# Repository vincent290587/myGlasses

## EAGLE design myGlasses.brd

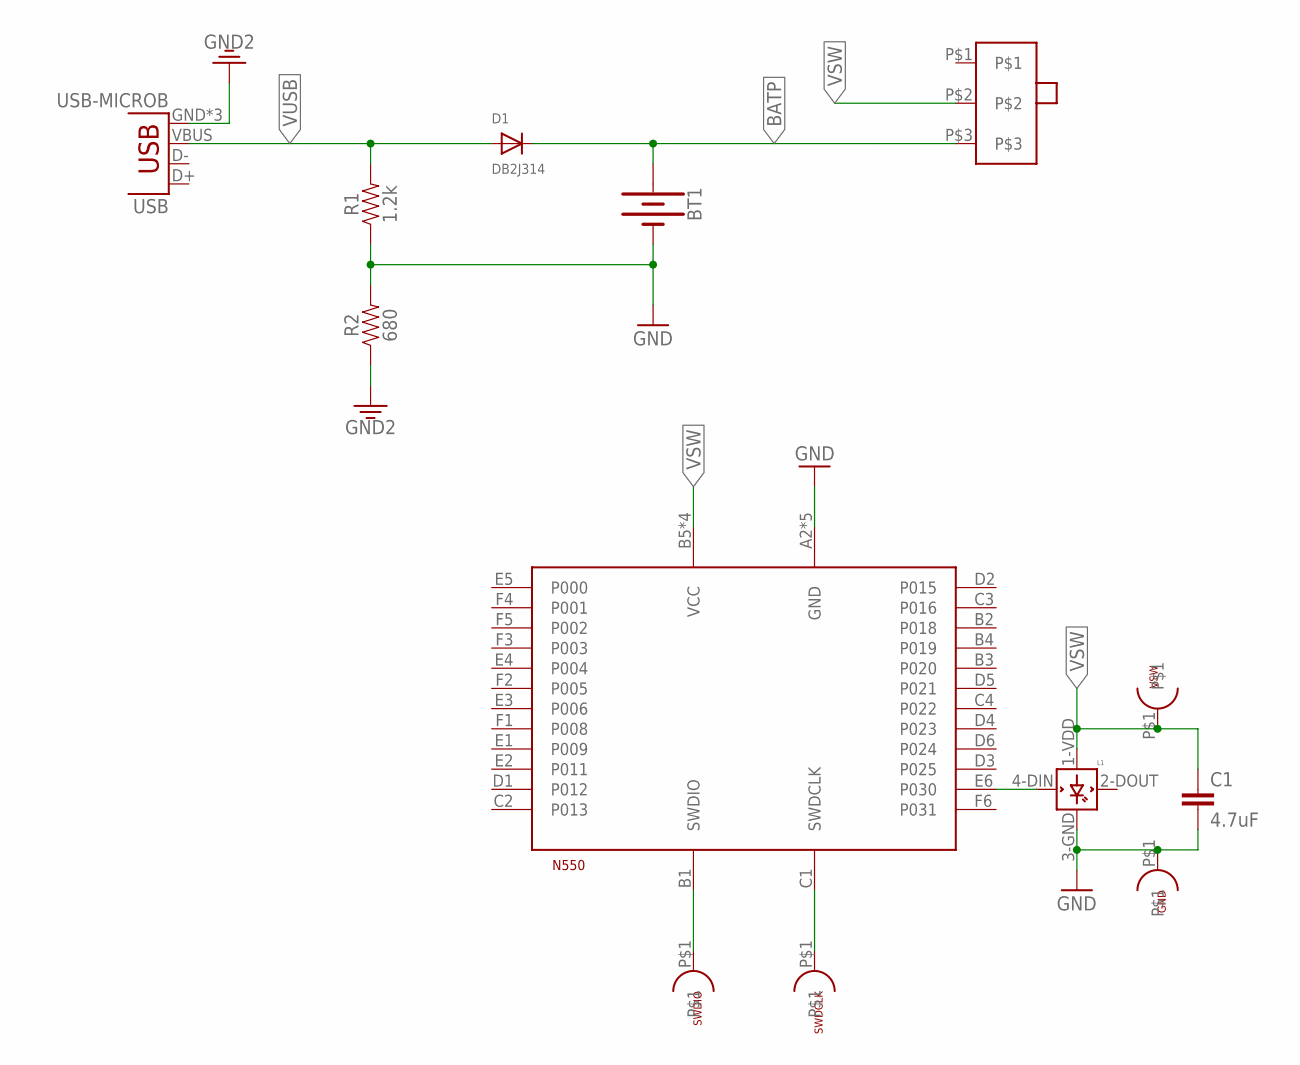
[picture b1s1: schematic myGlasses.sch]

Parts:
BT1: BATTERY-12MM_PTH; BATTCON_12MM_PTH
C1: 4.7uF; 0603
D1: DB2J314; SOD-323F
GND: TESTPOINT
L1: WS2812B
N550: N5150
R1: 1.2k; 0603
R2: 680; 0603
SWDCLK: TESTPOINT
SWDIO: TESTPOINT
U$1: JS102011SAQN
USB: USB-MICROB
VSW: TESTPOINT

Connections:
3.3V: R2.1, USB.GND, USB.MT1 (GND), USB.MT2 (GND)
BATP: BT1.VCC@1 (+), D1.C, U$1.P$3
GND: BT1.GND (-), C1.2, GND.P$1, L1.3-GND (GND), N550.A2 (GND), N550.A3 (GND), N550.A4 (GND), N550.A5 (GND), N550.A6 (GND), R1.1, R2.2
unnamed: N550.B1 (SWDIO), SWDIO.P$1
unnamed: N550.C1 (SWDCLK), SWDCLK.P$1
NEO: L1.4-DIN (DIN), N550.E6 (P030)
VSW: C1.1, L1.1-VDD (VDD), N550.B5 (VCC), N550.B6 (VCC), N550.C5 (VCC), N550.C6 (VCC), U$1.P$2, VSW.P$1
VUSB: D1.A, R1.2, USB.VBUS

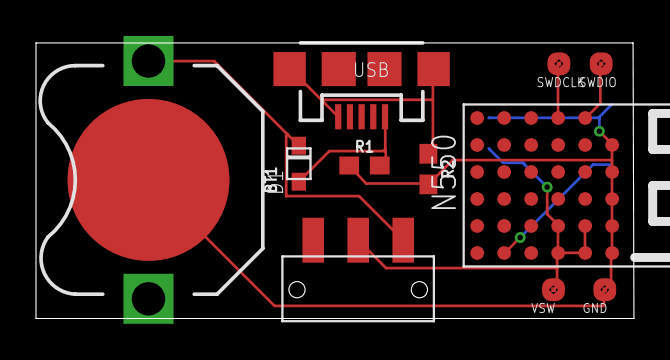
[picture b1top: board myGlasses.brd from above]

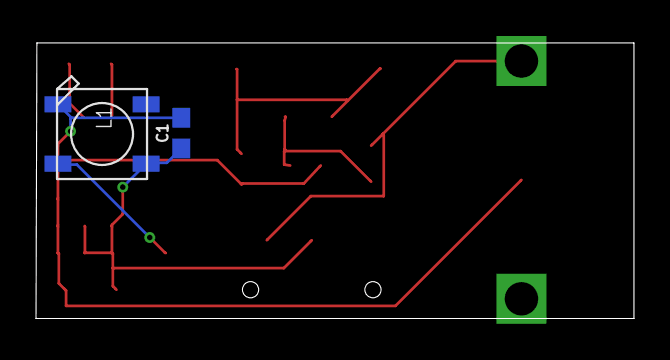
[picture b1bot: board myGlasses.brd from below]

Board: 2 copper layers, 33.2 x 15.3 mm, 13 parts (3 on the bottom side), 8 nets.

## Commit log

2015-10-29 Premier envoi seeedstudio
2015-12-26 Lunettes petit format corrige
2017-07-27 Put a ML1220 cell First routing

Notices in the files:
parts and their libraries:
SparkFun-Connectors: Licensing: Creative Commons ShareAlike 4.0 International - https://creativecommons.org/licenses/by-sa/4.0
